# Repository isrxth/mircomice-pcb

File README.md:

# Maze-X PCB

KiCad design files for a Raspberry Pi Pico-based maze robot controller. The board brings together motor control, sensor headers, power input, user controls, and expansion connectors on a single PCB.

## Highlights

- Raspberry Pi Pico controller
- L298N dual H-bridge motor driver
- Connections for two motors
- Infrared sensor and I2C-style sensor headers
- XT60 battery input and 5 V regulation
- Slide power switch and push buttons
- M3 mounting holes

## Project Files

| File | Description |
| --- | --- |
| `maze-x.kicad_sch` | Schematic |
| `maze-x.kicad_pcb` | PCB layout |
| `maze-x.kicad_pro` | KiCad project configuration |
| `images/` | Schematic and board screenshots |
| `maze-x-backups/` | KiCad backup files |

## Preview

### Schematic

### PCB Layout

### 3D View

## Opening the Project

1. Install [KiCad](https://www.kicad.org/).
2. Open `maze-x.kicad_pro` in KiCad.
3. Use the Schematic Editor to inspect the circuit and PCB Editor to inspect the board layout.

## Design Challenge

The main challenge was fitting the complete design onto a single-layer PCB while working to a strict deadline. This constraint influenced the routing, component placement, and board footprint, and is one reason a multilayer revision is planned for future development.

## Future Improvements

- Move to a multilayer PCB for improved routing, power distribution, and signal integrity.
- Increase the number of time-of-flight (ToF) sensors for more detailed maze and obstacle detection.
- Reduce the board footprint by optimizing component placement and connector locations.

## Status

This repository contains the current design files and visual previews. Review the schematic, run electrical-rule checks, and verify the board with your intended components and fabrication requirements before ordering.

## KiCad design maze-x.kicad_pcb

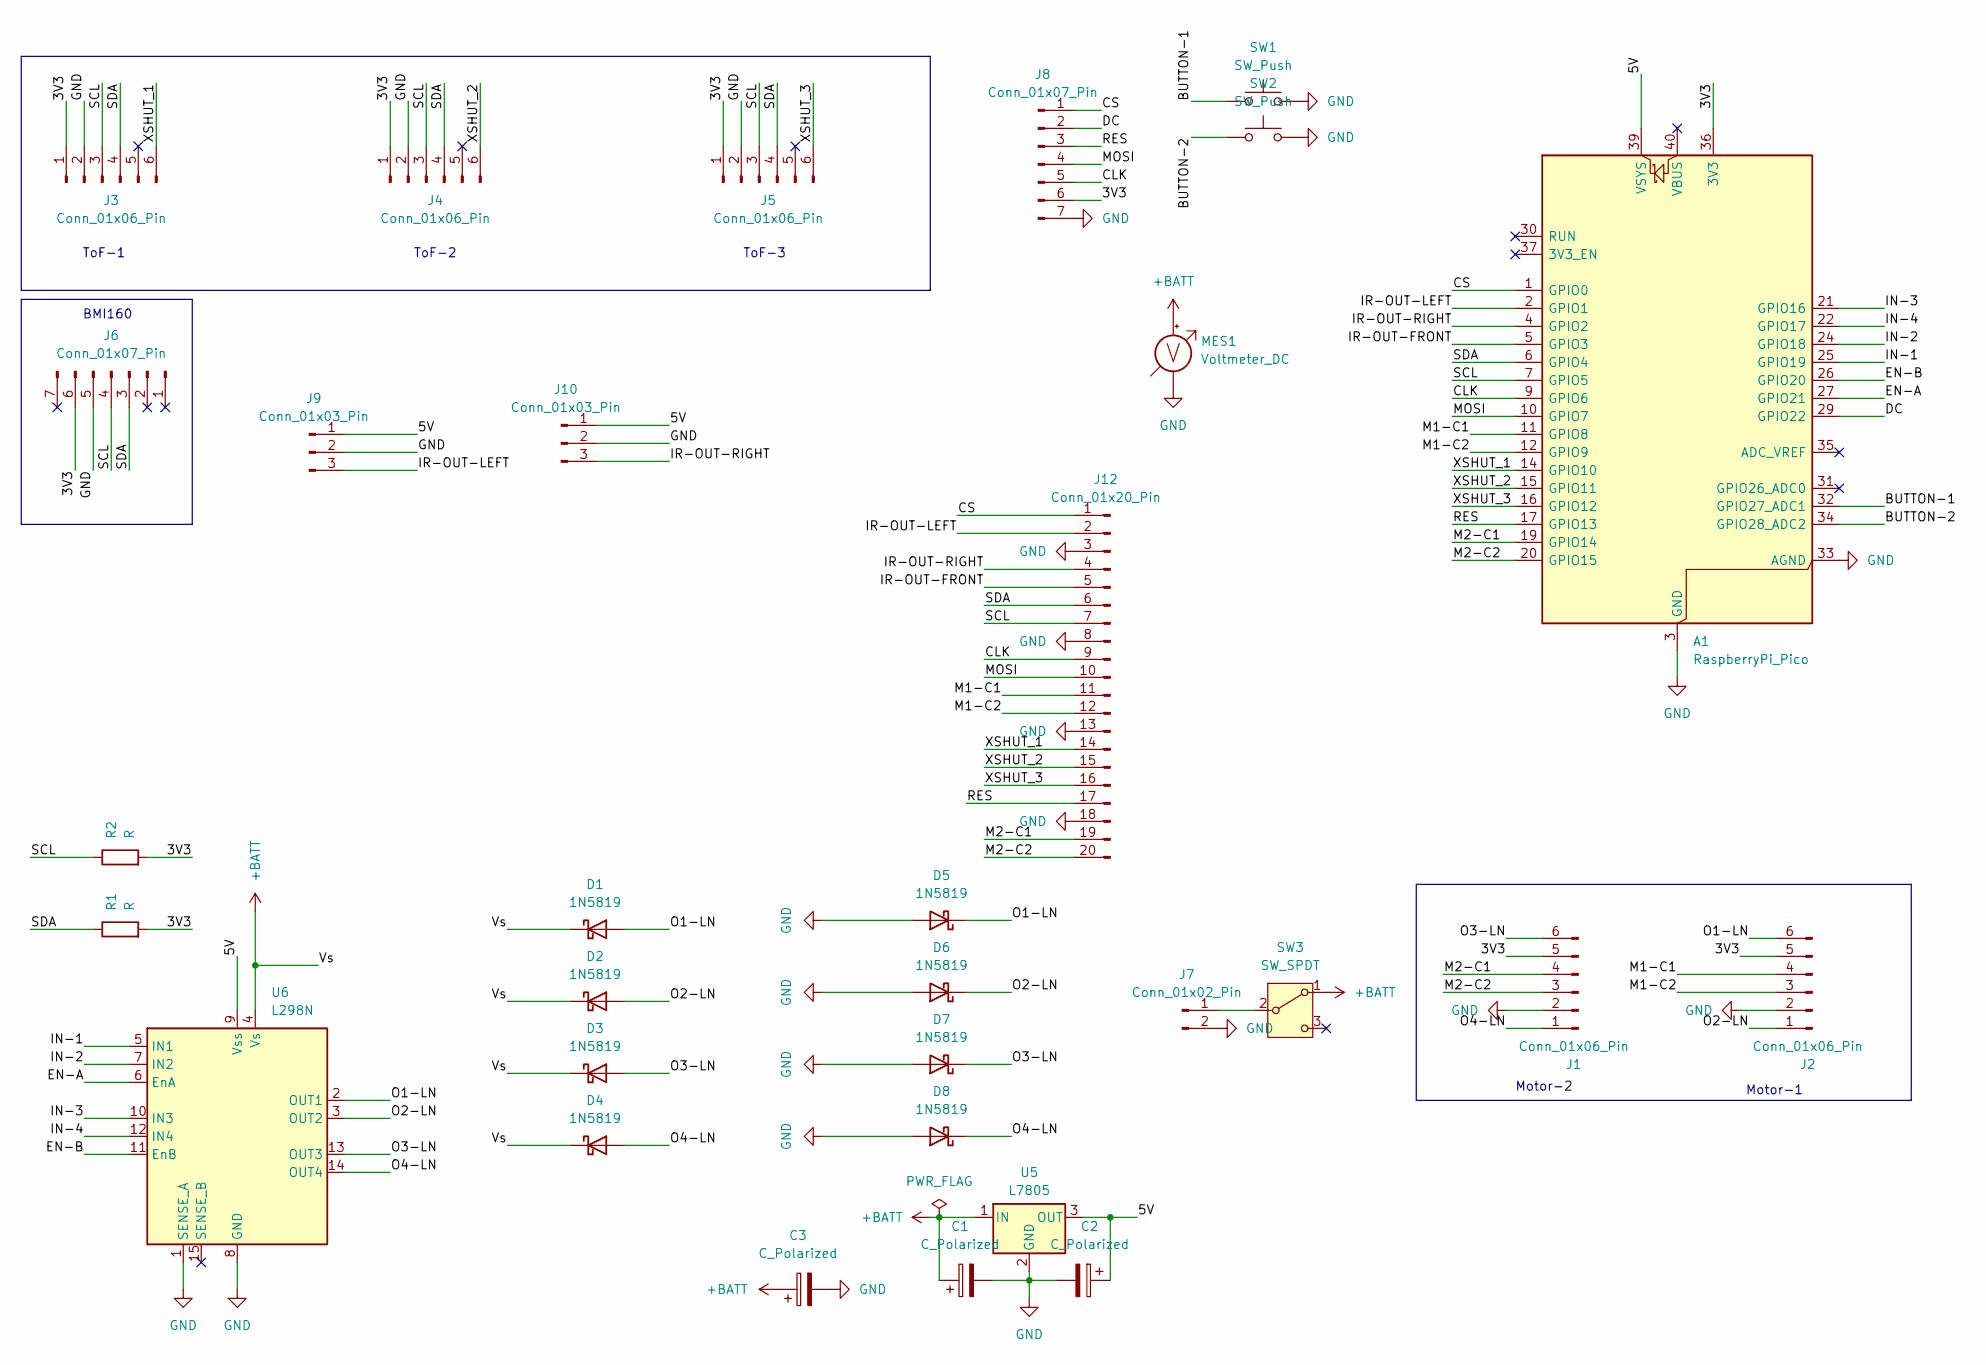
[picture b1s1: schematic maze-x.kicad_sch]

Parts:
A1: RaspberryPi_Pico; RaspberryPi_Pico_Common_Unspecified
C1, C2, C3: C_Polarized; CP_Radial_D5.0mm_P2.00mm
D1, D2, D3, D4, D5, D6, D7, D8: 1N5819; D_DO-41_SOD81_P10.16mm_Horizontal
J1, J2, J3, J4, J5: Conn_01x06_Pin; PinHeader_1x06_P2.54mm_Vertical
J6: Conn_01x07_Pin; PinHeader_1x07_P2.54mm_Vertical
J7: Conn_01x02_Pin; AMASS_XT60-M_1x02_P7.20mm_Vertical
J8: Conn_01x07_Pin; PinSocket_1x07_P2.54mm_Vertical
J9, J10: Conn_01x03_Pin; PinHeader_1x03_P2.54mm_Vertical
J12: Conn_01x20_Pin; PinHeader_1x20_P2.54mm_Vertical
MES1: Voltmeter_DC; PinHeader_1x02_P2.54mm_Vertical
R1, R2: R; R_Axial_DIN0207_L6.3mm_D2.5mm_P10.16mm_Horizontal
SW1, SW2: SW_Push; SW_PUSH_6mm_H4.3mm
SW3: SW_SPDT; SW_Slide_SPDT_Straight_CK_OS102011MS2Q
U5: L7805; TO-220-3_Vertical
U6: L298N; TO-220-15_P2.54x5.08mm_StaggerOdd_Lead4.58mm_Vertical

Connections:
+BATT: C1.1, C3.1, D1.1 (K), D2.1 (K), D3.1 (K), D4.1 (K), MES1.2 (+), SW3.1 (A), U5.1 (IN), U6.4 (Vs)
/3V3: A1.36 (3V3), J1.5, J2.5, J3.1, J4.1, J5.1, J6.6, J8.6, R1.2, R2.2
/5V: A1.39 (VSYS), C2.1, J9.1, J10.1, U5.3 (OUT), U6.9 (Vss)
/BUTTON-1: A1.32 (GPIO27_ADC1), SW1.1
/BUTTON-2: A1.34 (GPIO28_ADC2), SW2.1
/CLK: A1.9 (GPIO6), J8.5, J12.9
/CS: A1.1 (GPIO0), J8.1, J12.1
/DC: A1.29 (GPIO22), J8.2
/EN-A: A1.27 (GPIO21), U6.6 (EnA)
/EN-B: A1.26 (GPIO20), U6.11 (EnB)
/IN-1: A1.25 (GPIO19), U6.5 (IN1)
/IN-2: A1.24 (GPIO18), U6.7 (IN2)
/IN-3: A1.21 (GPIO16), U6.10 (IN3)
/IN-4: A1.22 (GPIO17), U6.12 (IN4)
/IR-OUT-FRONT: A1.5 (GPIO3), J12.5
/IR-OUT-LEFT: A1.2 (GPIO1), J9.3, J12.2
/IR-OUT-RIGHT: A1.4 (GPIO2), J10.3, J12.4
/M1-C1: A1.11 (GPIO8), J2.4, J12.11
/M1-C2: A1.12 (GPIO9), J2.3, J12.12
/M2-C1: A1.19 (GPIO14), J1.4, J12.19
/M2-C2: A1.20 (GPIO15), J1.3, J12.20
/MOSI: A1.10 (GPIO7), J8.4, J12.10
/O1-LN: D1.2 (A), D5.1 (K), J2.6, U6.2 (OUT1)
/O2-LN: D2.2 (A), D6.1 (K), J2.1, U6.3 (OUT2)
/O3-LN: D3.2 (A), D7.1 (K), J1.6, U6.13 (OUT3)
/O4-LN: D4.2 (A), D8.1 (K), J1.1, U6.14 (OUT4)
/RES: A1.17 (GPIO13), J8.3, J12.17
/SCL: A1.7 (GPIO5), J3.3, J4.3, J5.3, J6.4, J12.7, R2.1
/SDA: A1.6 (GPIO4), J3.4, J4.4, J5.4, J6.3, J12.6, R1.1
/XSHUT_1: A1.14 (GPIO10), J3.6, J12.14
/XSHUT_2: A1.15 (GPIO11), J4.6, J12.15
/XSHUT_3: A1.16 (GPIO12), J5.6, J12.16
GND: A1.3 (GND), A1.8 (GND), A1.13 (GND), A1.18 (GND), A1.23 (GND), A1.28 (GND), A1.33 (AGND), A1.38 (GND), C1.2, C2.2, C3.2, D5.2 (A), D6.2 (A), D7.2 (A), D8.2 (A), J1.2, J2.2, J3.2, J4.2, J5.2, J6.5, J7.2, J8.7, J9.2, J10.2, J12.3, J12.8, J12.13, J12.18, MES1.1 (-), SW1.2, SW2.2, U5.2 (GND), U6.1 (SENSE_A), U6.8 (GND)
unnamed: J7.1, SW3.2 (B)

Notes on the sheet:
Motor-1
Motor-2
ToF-3
ToF-2
BMI160
ToF-1

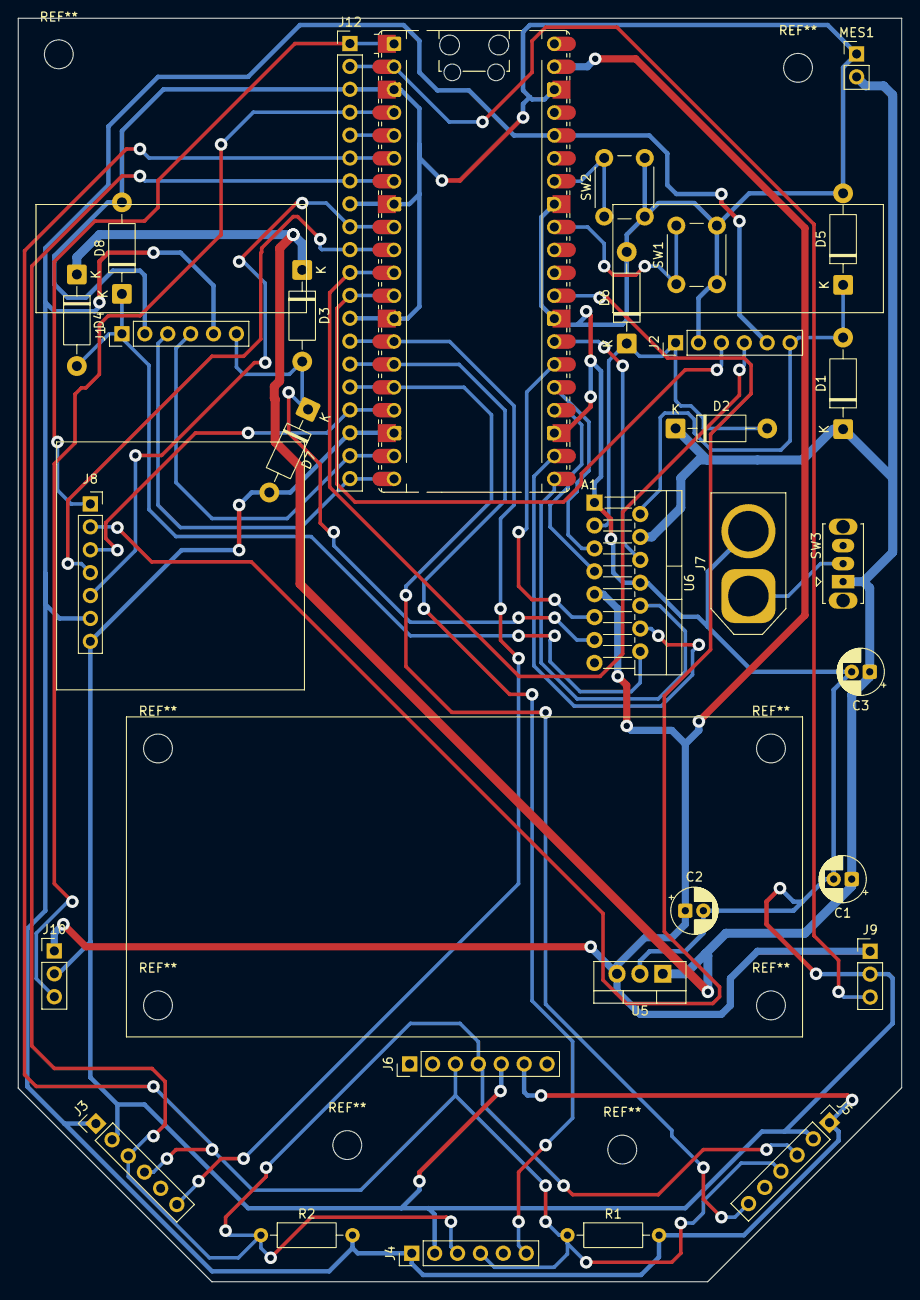
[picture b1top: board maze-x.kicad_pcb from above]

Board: 2 copper layers, 98.0 x 140.2 mm, 31 parts (0 on the bottom side), 34 nets.
